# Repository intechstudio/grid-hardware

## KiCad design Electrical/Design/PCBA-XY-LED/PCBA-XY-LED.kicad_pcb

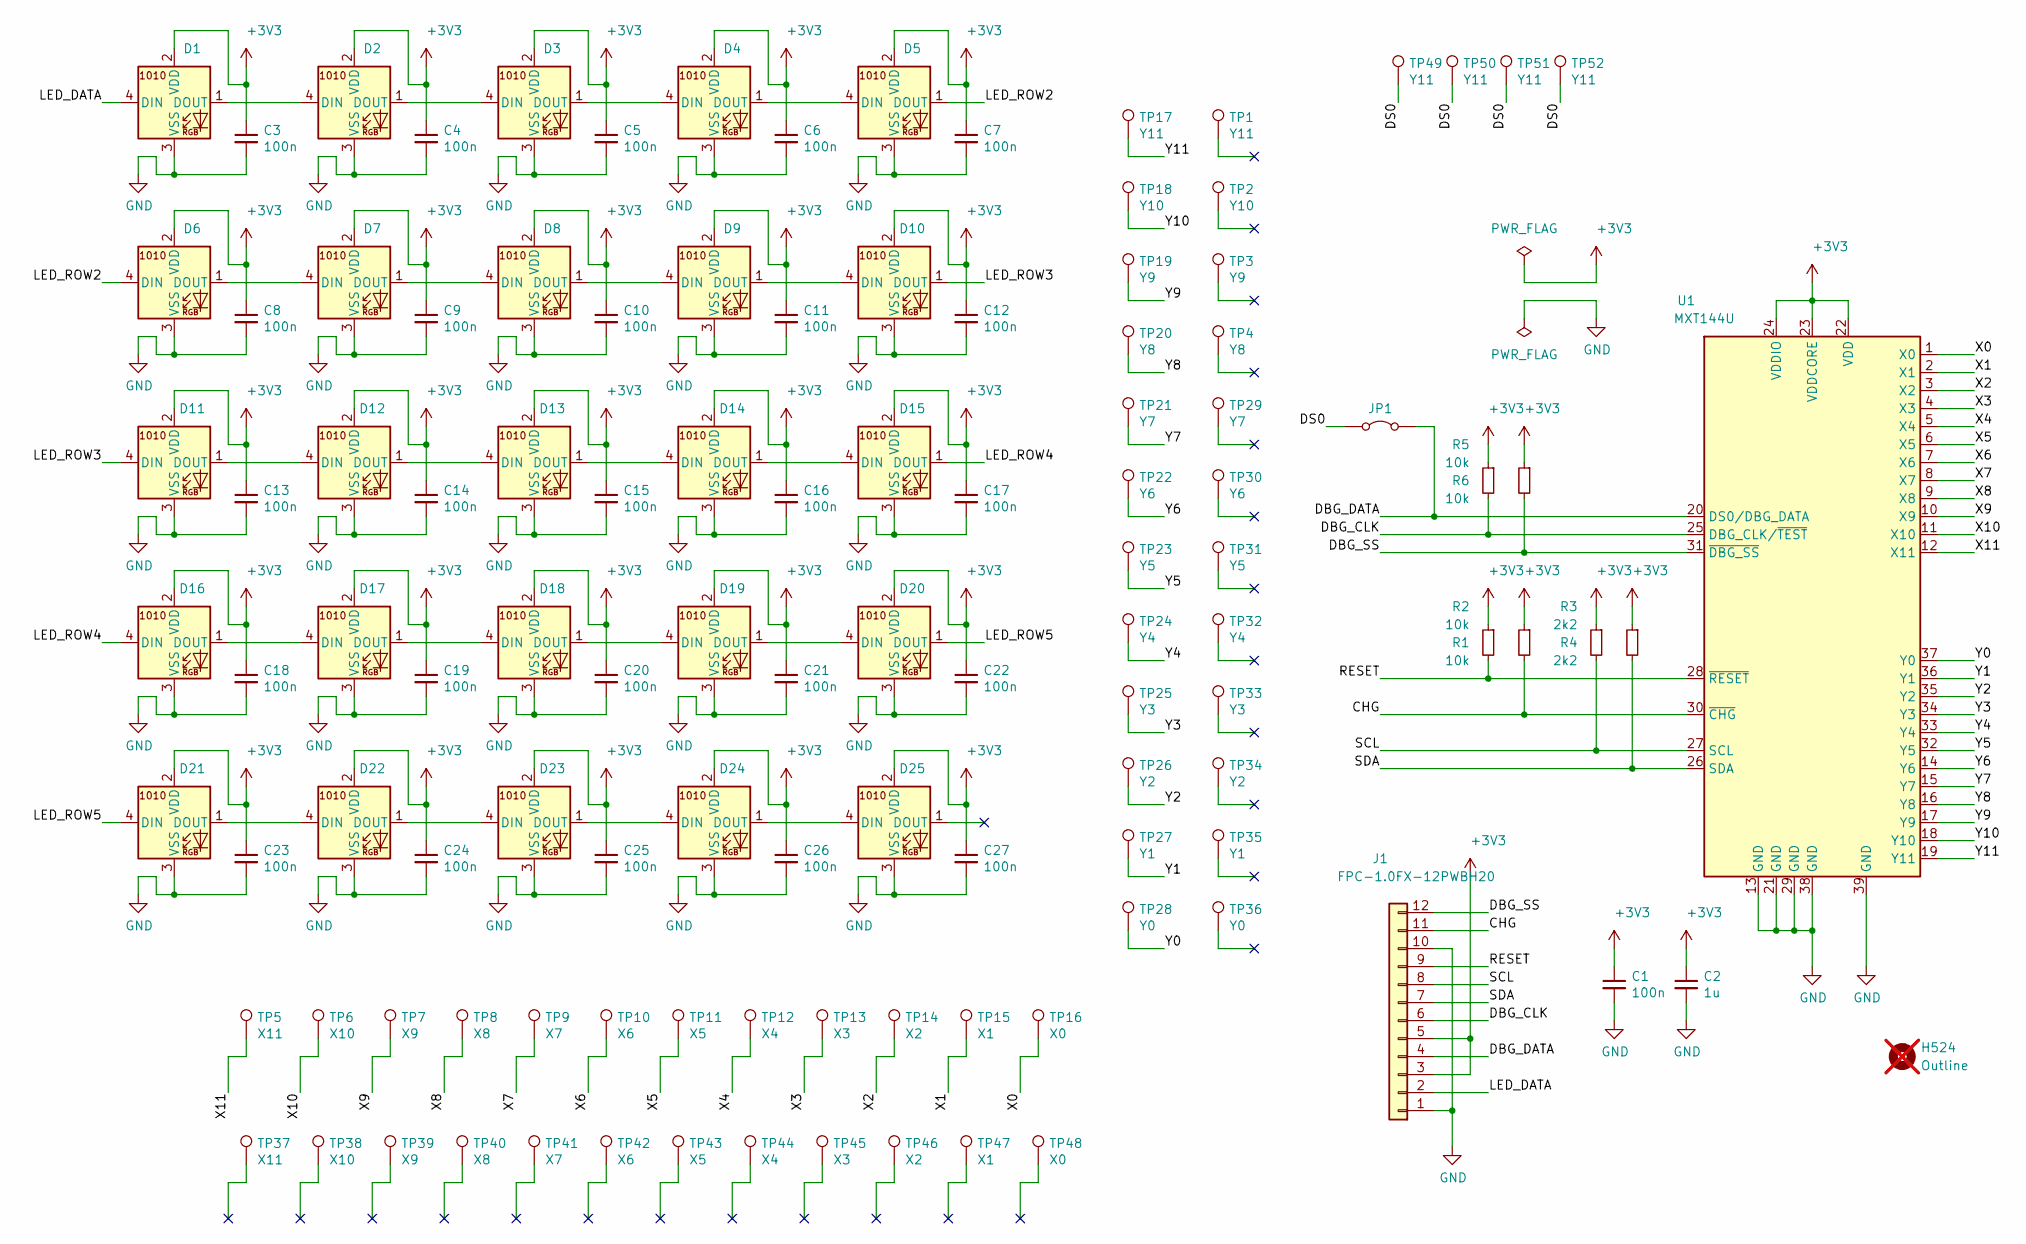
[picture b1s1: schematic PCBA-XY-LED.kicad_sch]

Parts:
C1, C3, C4, C5, C6, C7, C8, C9, C10, C11, C12, C13, C14, C15, C16, C17, C18, C19, C20, C21, C22, C23, C24, C25, C26, C27: 100n; CAP_0402
C2: 1u; CAP_0402
D1, D2, D3, D4, D5, D6, D7, D8, D9, D10, D11, D12, D13, D14, D15, D16, D17, D18, D19, D20, D21, D22, D23, D24, D25: UI_WS2812C-2020; LED-SMD_4P-L1.0-W1.0-TL_XL-1010RGBC-WS2812B
H524: Outline; OSHWA; not fitted
J1: FPC-1.0FX-12PWBH20; Molex_200528-0120_1x12-1MP_P1.00mm_Horizontal
JP1: Jumper_2_Bridged; SolderJumper-2_P1.3mm_Bridged_RoundedPad1.0x1.5mm
R1, R2, R5, R6: 10k; RES_0402
R3, R4: 2k2; RES_0402
TP1, TP17, TP49, TP50, TP51, TP52: Y11; CASTELLATED_XY_HOLE
TP2, TP18: Y10; CASTELLATED_XY_HOLE
TP3, TP19: Y9; CASTELLATED_XY_HOLE
TP4, TP20: Y8; CASTELLATED_XY_HOLE
TP5, TP37: X11; CASTELLATED_XY_HOLE
TP6, TP38: X10; CASTELLATED_XY_HOLE
TP7, TP39: X9; CASTELLATED_XY_HOLE
TP8, TP40: X8; CASTELLATED_XY_HOLE
TP9, TP41: X7; CASTELLATED_XY_HOLE
TP10, TP42: X6; CASTELLATED_XY_HOLE
TP11, TP43: X5; CASTELLATED_XY_HOLE
TP12, TP44: X4; CASTELLATED_XY_HOLE
TP13, TP45: X3; CASTELLATED_XY_HOLE
TP14, TP46: X2; CASTELLATED_XY_HOLE
TP15, TP47: X1; CASTELLATED_XY_HOLE
TP16, TP48: X0; CASTELLATED_XY_HOLE
TP21, TP29: Y7; CASTELLATED_XY_HOLE
TP22, TP30: Y6; CASTELLATED_XY_HOLE
TP23, TP31: Y5; CASTELLATED_XY_HOLE
TP24, TP32: Y4; CASTELLATED_XY_HOLE
TP25, TP33: Y3; CASTELLATED_XY_HOLE
TP26, TP34: Y2; CASTELLATED_XY_HOLE
TP27, TP35: Y1; CASTELLATED_XY_HOLE
TP28, TP36: Y0; CASTELLATED_XY_HOLE
U1: MXT144U; QFN-38_EP_4x4_Pitch0.35mm

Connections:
+3V3: C1.1, C2.1, C3.1, C4.1, C5.1, C6.1, C7.1, C8.1, C9.1, C10.1, C11.1, C12.1, C13.1, C14.1, C15.1, C16.1, C17.1, C18.1, C19.1, C20.1, C21.1, C22.1, C23.1, C24.1, C25.1, C26.1, C27.1, D1.2 (VDD), D2.2 (VDD), D3.2 (VDD), D4.2 (VDD), D5.2 (VDD), D6.2 (VDD), D7.2 (VDD), D8.2 (VDD), D9.2 (VDD), D10.2 (VDD), D11.2 (VDD), D12.2 (VDD), D13.2 (VDD), D14.2 (VDD), D15.2 (VDD), D16.2 (VDD), D17.2 (VDD), D18.2 (VDD), D19.2 (VDD), D20.2 (VDD), D21.2 (VDD), D22.2 (VDD), D23.2 (VDD), D24.2 (VDD), D25.2 (VDD), J1.3, J1.5, R1.1, R2.1, R3.1, R4.1, R5.1, R6.1, U1.22 (VDD), U1.23 (VDDCORE), U1.24 (VDDIO)
/CHG: J1.11, R1.2, U1.30 (~CHG)
/DBG_CLK: J1.6, R5.2, U1.25 (DBG_CLK/~TEST)
/DBG_DATA: J1.4, JP1.2 (B), U1.20 (DS0/DBG_DATA)
/DBG_SS: J1.12, R6.2, U1.31 (~DBG_SS)
/DS0: JP1.1 (A), TP49.1, TP50.1, TP51.1, TP52.1
/LED_DATA: D1.4 (DIN), J1.2
/LED_ROW2: D5.1 (DOUT), D6.4 (DIN)
/LED_ROW3: D10.1 (DOUT), D11.4 (DIN)
/LED_ROW4: D15.1 (DOUT), D16.4 (DIN)
/LED_ROW5: D20.1 (DOUT), D21.4 (DIN)
/RESET: J1.9, R2.2, U1.28 (~RESET)
/SCL: J1.8, R3.2, U1.27 (SCL)
/SDA: J1.7, R4.2, U1.26 (SDA)
/X0: TP16.1, U1.1 (X0)
/X1: TP15.1, U1.2 (X1)
/X2: TP14.1, U1.3 (X2)
/X3: TP13.1, U1.4 (X3)
/X4: TP12.1, U1.5 (X4)
/X5: TP11.1, U1.6 (X5)
/X6: TP10.1, U1.7 (X6)
/X7: TP9.1, U1.8 (X7)
/X8: TP8.1, U1.9 (X8)
/X9: TP7.1, U1.10 (X9)
/X10: TP6.1, U1.11 (X10)
/X11: TP5.1, U1.12 (X11)
/Y0: TP28.1, U1.37 (Y0)
/Y1: TP27.1, U1.36 (Y1)
/Y2: TP26.1, U1.35 (Y2)
/Y3: TP25.1, U1.34 (Y3)
/Y4: TP24.1, U1.33 (Y4)
/Y5: TP23.1, U1.32 (Y5)
/Y6: TP22.1, U1.14 (Y6)
/Y7: TP21.1, U1.15 (Y7)
/Y8: TP20.1, U1.16 (Y8)
/Y9: TP19.1, U1.17 (Y9)
/Y10: TP18.1, U1.18 (Y10)
/Y11: TP17.1, U1.19 (Y11)
GND: C1.2, C2.2, C3.2, C4.2, C5.2, C6.2, C7.2, C8.2, C9.2, C10.2, C11.2, C12.2, C13.2, C14.2, C15.2, C16.2, C17.2, C18.2, C19.2, C20.2, C21.2, C22.2, C23.2, C24.2, C25.2, C26.2, C27.2, D1.3 (VSS), D2.3 (VSS), D3.3 (VSS), D4.3 (VSS), D5.3 (VSS), D6.3 (VSS), D7.3 (VSS), D8.3 (VSS), D9.3 (VSS), D10.3 (VSS), D11.3 (VSS), D12.3 (VSS), D13.3 (VSS), D14.3 (VSS), D15.3 (VSS), D16.3 (VSS), D17.3 (VSS), D18.3 (VSS), D19.3 (VSS), D20.3 (VSS), D21.3 (VSS), D22.3 (VSS), D23.3 (VSS), D24.3 (VSS), D25.3 (VSS), J1.1, J1.10, U1.13 (GND), U1.21 (GND), U1.29 (GND), U1.38 (GND), U1.39 (GND)
unnamed: D1.1 (DOUT), D2.4 (DIN)
unnamed: D2.1 (DOUT), D3.4 (DIN)
unnamed: D3.1 (DOUT), D4.4 (DIN)
unnamed: D4.1 (DOUT), D5.4 (DIN)
unnamed: D6.1 (DOUT), D7.4 (DIN)
unnamed: D7.1 (DOUT), D8.4 (DIN)
unnamed: D8.1 (DOUT), D9.4 (DIN)
unnamed: D9.1 (DOUT), D10.4 (DIN)
unnamed: D11.1 (DOUT), D12.4 (DIN)
unnamed: D12.1 (DOUT), D13.4 (DIN)
unnamed: D13.1 (DOUT), D14.4 (DIN)
unnamed: D14.1 (DOUT), D15.4 (DIN)
unnamed: D16.1 (DOUT), D17.4 (DIN)
unnamed: D17.1 (DOUT), D18.4 (DIN)
unnamed: D18.1 (DOUT), D19.4 (DIN)
unnamed: D19.1 (DOUT), D20.4 (DIN)
unnamed: D21.1 (DOUT), D22.4 (DIN)
unnamed: D22.1 (DOUT), D23.4 (DIN)
unnamed: D23.1 (DOUT), D24.4 (DIN)
unnamed: D24.1 (DOUT), D25.4 (DIN)

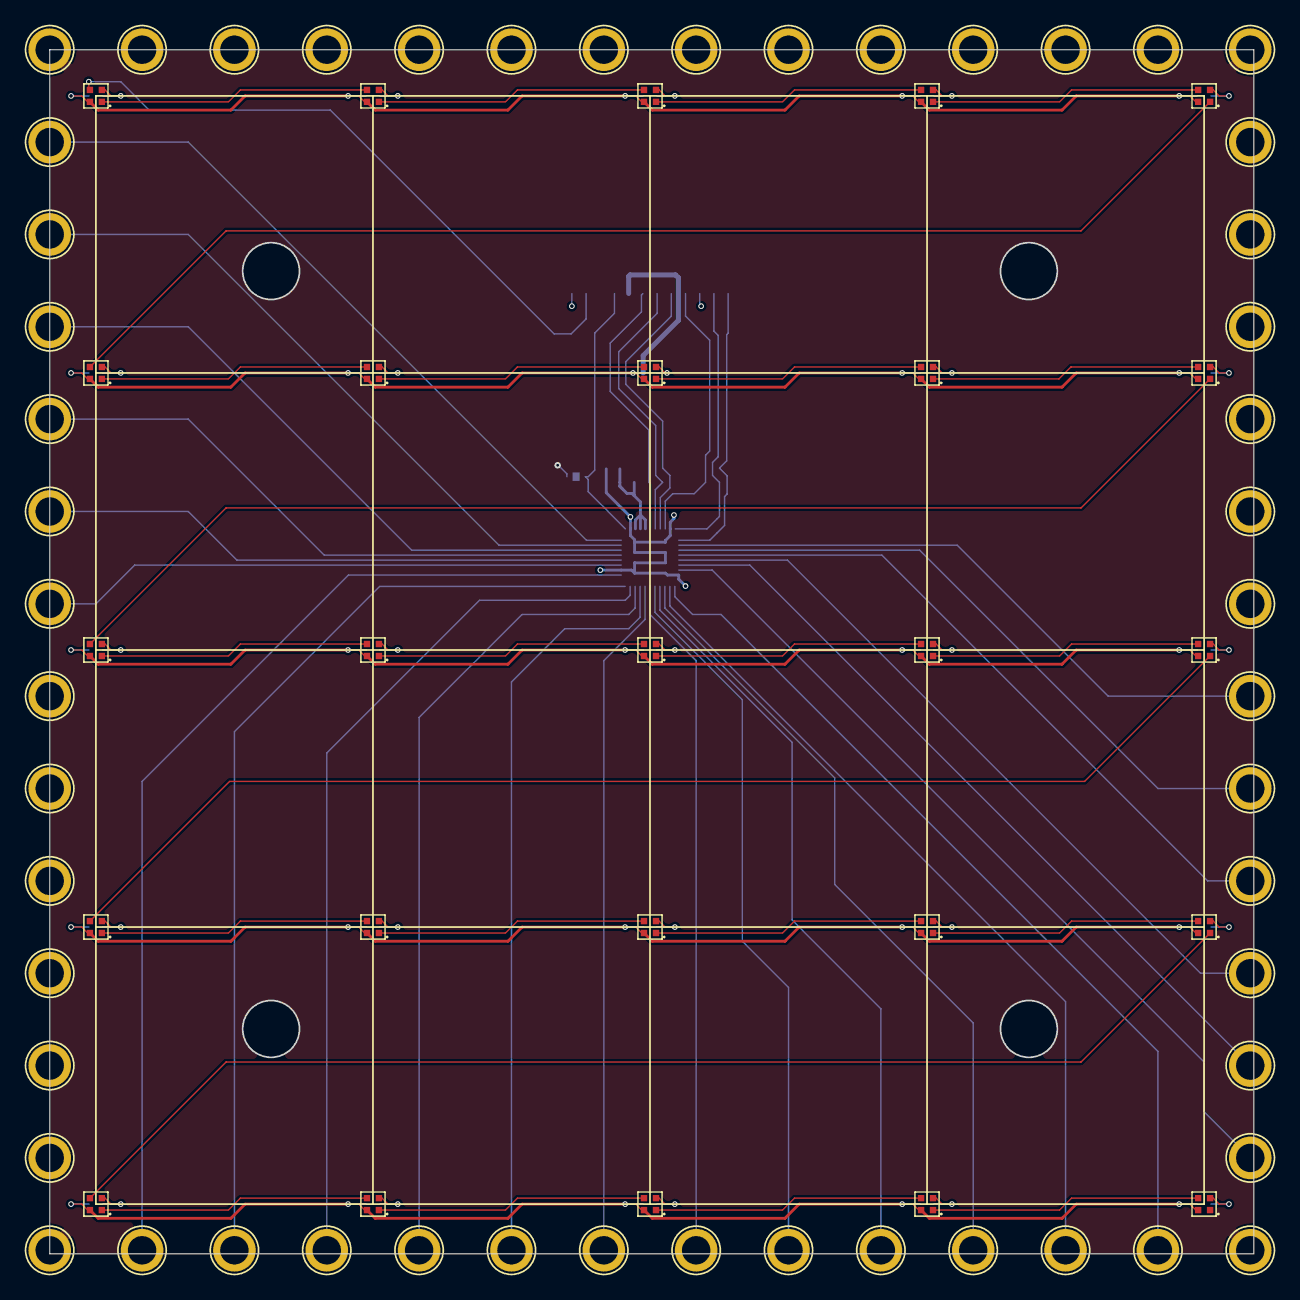
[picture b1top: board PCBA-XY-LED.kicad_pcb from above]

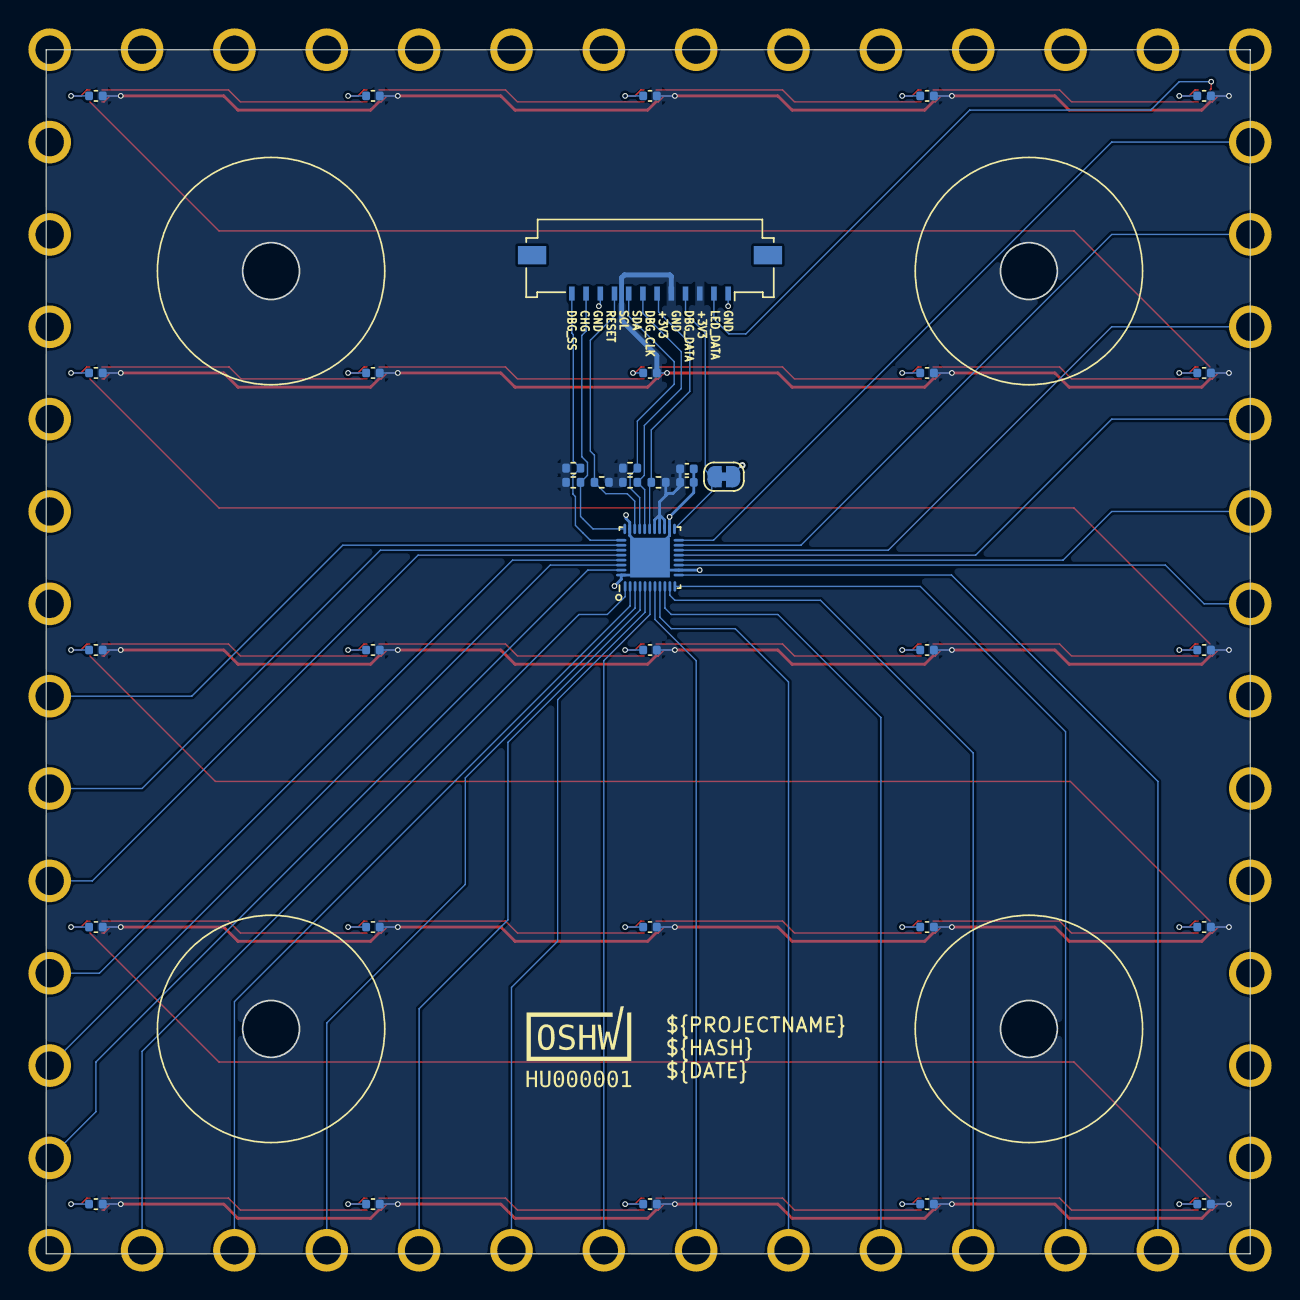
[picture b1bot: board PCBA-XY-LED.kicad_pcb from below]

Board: 4 copper layers, 84.8 x 84.8 mm, 114 parts (37 on the bottom side), 59 nets.

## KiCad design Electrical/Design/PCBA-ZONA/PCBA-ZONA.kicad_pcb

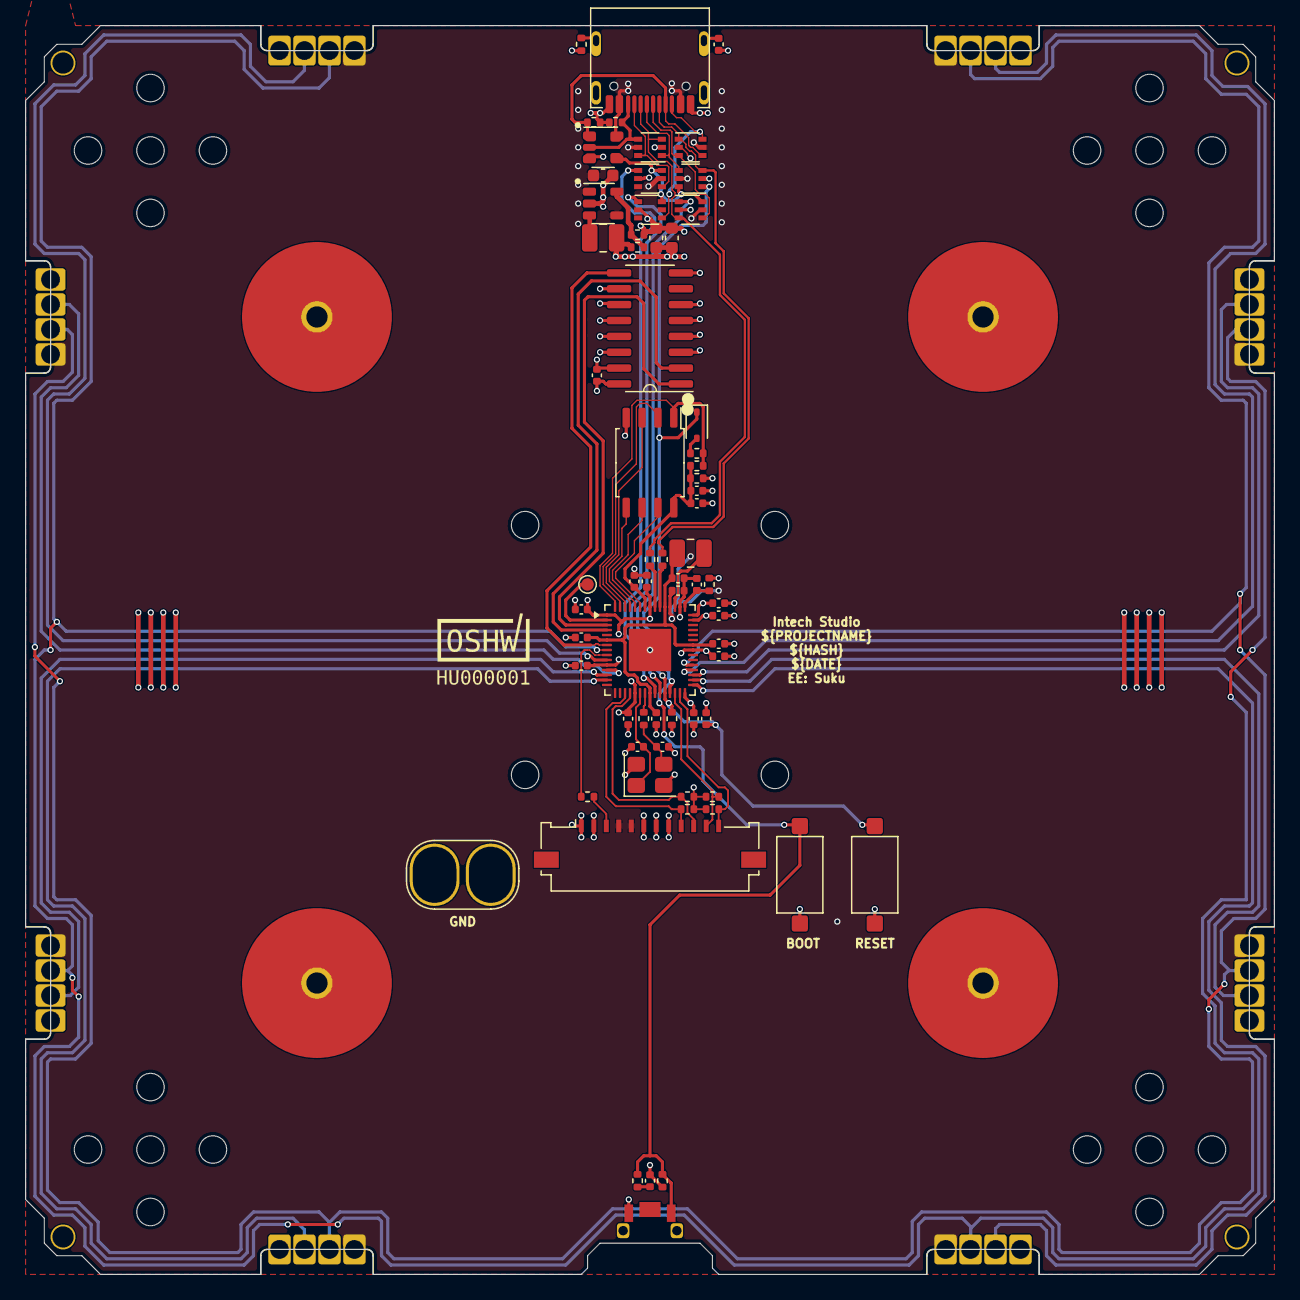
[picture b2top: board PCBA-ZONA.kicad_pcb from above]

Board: 4 copper layers, 100.0 x 100.0 mm, 78 parts (0 on the bottom side), 57 nets.

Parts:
C201, C214, C216: 4u7; CAP_0402
C202, C203, C204, C205, C206, C207, C208, C209, C210, C211, C212, C213, C215, C221, C501: 100n; CAP_0402
C217, C220: 1u; CAP_0402
C218, C219: 10p; CAP_0402
C301: 4n7; CAP_0402
C302, C303, C304: 22u; CAP_0603
D201: 1N5819WS; D_SOD-323
J201: Conn_01x02; OscilloscopeGround
J301: TYPE-C-32-M-12; USB_C_Korean_Hroparts_TYPE-C-31-M-12
J401, J402, J403, J404, J405, J406, J407, J408: Conn_01x04; J_INTERFACE_SPRINGPATTERN
J601: FPC-1.0FX-12PWBH20; Molex_200528-0120_1x12-1MP_P1.00mm_Horizontal
L201, L301: GXTC252010-3R3-MT; L_1008_2520Metric
LOGO201: OSHWA
M401: Conn_01x08; grid_outline
R201, R605: 0R; RES_0402
R202, R205, R209: 1k; RES_0402
R203, R207, R208: 27R; RES_0402
R204: 10k; RES_0402
R206, R301, R302: 5k1; RES_0402
R210, R305, R601, R602, R603, R604: 100k; RES_0402
R303: 1M; RES_0402
R304: 450k; RES_0402
SW201: C255807; SW_HYP_MAPMODE
SW202, SW203: C2905169; SW_SPST_CK_RS282G05A3
TP201: SPICS1; TestPoint_Pad_D1.0mm
U201: RP2350A; QFN-60-1EP_7x7mm_P0.4mm_EP3.4x3.4mm
U202: GD25B64ESIGR; SOIC-8W_FLASH
U301, U304, U306, U307: BL1551B; SOT-363_SC-70-6
U302, U305: ESDU5V0K4; SOT-363_SC-70-6
U303: 74LVC1G08; SOT-23-5-AND-TSSOP5
U308: RY3409; SOT-23-5
U501: 74HC165; SOIC-16_74HC165
Y201: 12MHz; Crystal_SMD_Abracon_ABM8G-4Pin_3.2x2.5mm

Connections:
+1V1: C211.1, C212.1, C213.1, C214.1, L201.2, U201.6 (DVDD), U201.23 (DVDD), U201.39 (DVDD), U201.50 (VREG_FB)
+3V3: C202.1, C203.1, C204.1, C205.1, C206.1, C207.1, C208.1, C209.1, C215.2, C303.1, C304.1, C501.1, J601.8, L301.2, R201.1, R203.1, R204.1, R206.1, R304.1, R601.1, R602.1, R603.1, R604.1, U201.1 (IOVDD), U201.11 (IOVDD), U201.20 (IOVDD), U201.30 (IOVDD), U201.38 (IOVDD), U201.44 (ADC_AVDD), U201.45 (IOVDD), U201.53 (USB_OTP_VDD), U501.4 (D5), U501.5 (D6), U501.11 (D0), U501.13 (D2), U501.16 (VCC)
+5V: C201.1, C302.1, J301.A4B9 (VBUS), J301.A9B4 (VBUS), J401.1, J402.4, J403.1, J404.4, J405.4, J406.1, J407.4, J408.1, J601.4, J601.5, U201.49 (VREG_VIN), U301.5 (VCC), U302.5, U303.5 (VCC), U304.5 (VCC), U305.5, U306.5 (VCC), U307.5 (VCC), U308.1 (CE), U308.4 (VIN)
/HWCFG/HWCFG_CLOCK: U201.4 (GPIO2), U501.2 (CLK)
/HWCFG/HWCFG_DATA_IN: U201.7 (GPIO4), U501.9 (Q)
/HWCFG/HWCFG_SHIFT: U201.3 (GPIO1), U501.1 (SH/~LD)
/MCU/GPIO17: J601.11, R602.2, U201.28 (GPIO17)
/MCU/GPIO18: J601.12, R601.2, U201.29 (GPIO18)
/MCU/GRID_EAST_RX: J403.3, U201.33 (GPIO21)
/MCU/GRID_EAST_TX: J405.2, U201.32 (GPIO20)
/MCU/GRID_NORTH_RX: J401.3, U201.10 (GPIO7)
/MCU/GRID_NORTH_TX: J402.2, U201.34 (GPIO22)
/MCU/GRID_SOUTH_RX: J408.3, U201.31 (GPIO19)
/MCU/GRID_SOUTH_TX: J407.2, U201.14 (GPIO10)
/MCU/GRID_SYNC_1: J402.3, J404.3, J405.3, J407.3, U201.35 (GPIO23)
/MCU/GRID_SYNC_2: J401.2, J403.2, J406.2, J408.2, U201.8 (GPIO5)
/MCU/GRID_WEST_RX: J406.3, U201.13 (GPIO9)
/MCU/GRID_WEST_TX: J404.2, U201.12 (GPIO8)
/MCU/LED_DATA_OUT: R605.1, U201.9 (GPIO6)
/MCU/MAP_MODE: D201.1 (K), R204.2, R205.2, SW201.1 (A), SW202.1 (A), U201.27 (GPIO16), U306.1 (A1)
/MCU/RESET: C217.1, R206.2, SW203.1 (A), U201.26 (RUN), U307.1 (A1)
/MCU/RP_SWCLK: U201.24 (SWCLK), U301.1 (A1)
/MCU/RP_SWDIO: U201.25 (SWDIO), U304.1 (A1)
/MCU/SCL: J601.10, R603.2, U201.19 (GPIO15)
/MCU/SDA: J601.9, R604.2, U201.18 (GPIO14)
/MCU/SPICLK: U201.56 (QSPI_SCLK), U202.6 (CLK)
/MCU/SPICS0: R202.2, R210.2, U201.60 (~QSPI_SS), U202.1 (~CS)
/MCU/SPICS1: TP201.1 (1_1), U201.2 (GPIO0)
/MCU/SPID: U201.57 (QSPI_SD0), U202.5 (DI(IO0))
/MCU/SPIHD: U201.55 (QSPI_SD3), U202.7 (IO3)
/MCU/SPIQ: U201.59 (QSPI_SD1), U202.2 (DO(IO1))
/MCU/SPIWP: U201.58 (QSPI_SD2), U202.3 (IO2)
/MCU/USB_DN: J301.B7 (D-), R207.1, U302.1, U306.3 (A2)
/MCU/USB_DP: J301.B6 (D+), R208.1, U305.3, U307.3 (A2)
/MCU/USB_POWER/A6: J301.A6 (D+), U302.3, U307.4 (B)
/MCU/USB_POWER/A7: J301.A7 (D-), U305.1, U306.4 (B)
/MCU/USB_POWER/CC1: J301.A5 (CC1), R301.1, U302.4, U303.1
/MCU/USB_POWER/CC2: J301.B5 (CC2), R302.1, U303.2, U305.4
/MCU/USB_POWER/DEBUG: U301.6 (EN_A1), U303.4, U304.6 (EN_A1), U306.6 (EN_A1), U307.6 (EN_A1)
/MCU/USB_POWER/SBU1: J301.A8 (SBU1), U301.4 (B), U305.6
/MCU/USB_POWER/SBU2: J301.B8 (SBU2), U302.6, U304.4 (B)
GND: C201.2, C202.2, C203.2, C204.2, C205.2, C206.2, C207.2, C208.2, C209.2, C210.2, C211.2, C212.2, C213.2, C214.2, C216.2, C217.2, C218.2, C219.2, C220.2, C221.2, C301.2, C302.2, C303.2, C304.2, C501.2, J201.1, J201.2, J301.A1B12 (GND), J301.A12B1 (GND), J401.4, J402.1, J403.4, J404.1, J405.1, J406.4, J407.1, J408.4, J601.1, J601.2, J601.6, J601.7, R301.2, R302.2, R303.2, R305.2, SW201.2 (B), SW202.2 (B), SW203.2 (B), U201.47 (VREG_PGND), U201.61 (GND), U202.4 (GND), U301.2 (GND), U302.2, U303.3 (GND), U304.2 (GND), U305.2, U306.2 (GND), U307.2 (GND), U308.2 (GND), U501.3 (D4), U501.6 (D7), U501.8 (GND), U501.10 (SI), U501.12 (D1), U501.14 (D3), U501.15 (INH), Y201.2, Y201.4
unnamed: C215.1, R205.1
unnamed: C219.1, R209.2, Y201.3
unnamed: C301.1, J301.S3 (SHIELD)
unnamed: D201.2 (A), R202.1
unnamed: J301.S4 (SHIELD), R303.1
unnamed: J601.3, R605.2
unnamed: R207.2, U201.51 (USB_DM)
unnamed: R208.2, U201.52 (USB_DP)
unnamed: C216.1, R203.2, U201.46 (VREG_AVDD)
unnamed: L201.1, U201.48 (VREG_LX)
unnamed: C218.1, U201.21 (XIN), Y201.1
unnamed: R209.1, U201.22 (XOUT)
unnamed: R304.2, R305.1, U308.5 (FB)
unnamed: L301.1, U308.3 (LX)
VDD_SPI: C210.1, C220.1, C221.1, R201.2, R210.1, U201.54 (QSPI_IOVDD), U202.8 (VCC)
